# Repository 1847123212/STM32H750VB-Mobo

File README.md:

# STM32H750VB-Mobo
Motherboard for STM32H750VB Coreboard

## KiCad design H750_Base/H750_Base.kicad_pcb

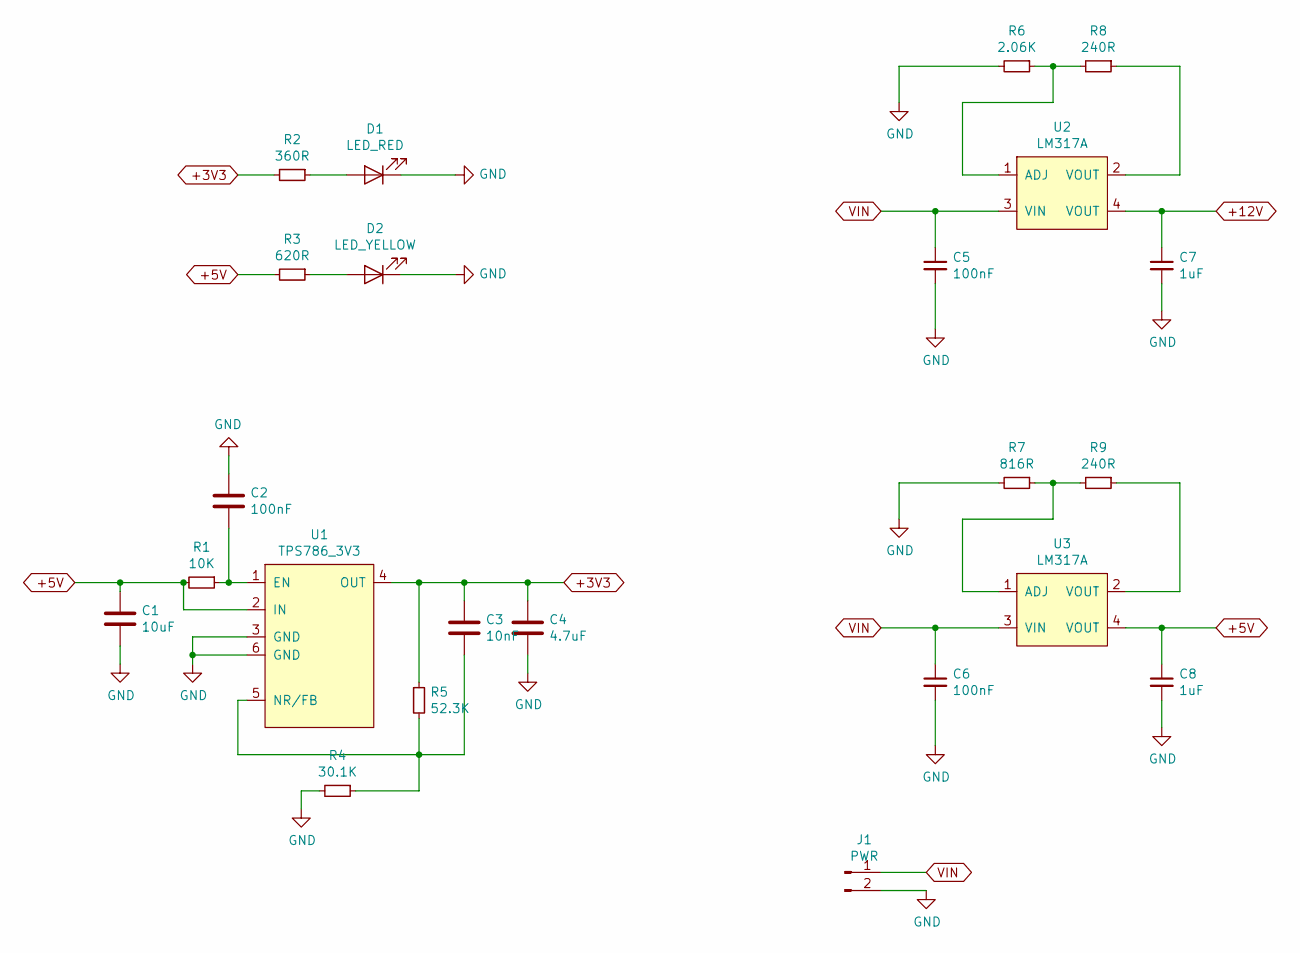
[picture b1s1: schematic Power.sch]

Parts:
C1: 10uF; C_0603_1608Metric
C2: 100nF; C_0603_1608Metric
C3: 10nF; C_0603_1608Metric
C4: 4.7uF; C_0603_1608Metric
C5, C6: 100nF; C_1206_3216Metric
C7, C8: 1uF; C_0805_2012Metric
D1: LED_RED; LED_0603_1608Metric
D2: LED_YELLOW; LED_0603_1608Metric
J1: PWR; PhoenixContact_MSTBVA_2,5_2-G-5,08_1x02_P5.08mm_Vertical
R1: 10K; R_0603_1608Metric
R2: 360R; R_0603_1608Metric
R3: 620R; R_0603_1608Metric
R4: 30.1K; R_0603_1608Metric
R5: 52.3K; R_0603_1608Metric
R6: 2.06K; R_0603_1608Metric
R7: 816R; R_0603_1608Metric
R8, R9: 240R; R_0603_1608Metric
U1: TPS786_3V3; SOT-223-6
U2, U3: LM317A; SOT-223

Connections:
+3V3: C3.1, C4.1, R2.2, R5.1, U1.4 (OUT); also elsewhere on the board
+5V: C1.1, C8.1, R1.2, R3.2, U1.2 (IN), U3.4 (VOUT); also elsewhere on the board
+12V: C7.1, U2.4 (VOUT); also elsewhere on the board
GND: C1.2, C2.1, C4.2, C5.2, C6.2, C7.2, C8.2, D1.1 (K), D2.1 (K), J1.2, R4.2, R6.2, R7.2, U1.3 (GND), U1.6 (GND); also elsewhere on the board
unnamed: C2.2, R1.1, U1.1 (EN)
unnamed: C3.2, R4.1, R5.2, U1.5 (NR/FB)
unnamed 87: D1.2 (A), R2.1; also elsewhere on the board
unnamed 88: D2.2 (A), R3.1; also elsewhere on the board
unnamed: R6.1, R8.2, U2.1 (ADJ)
unnamed: R7.1, R9.2, U3.1 (ADJ)
unnamed: R8.1, U2.2 (VOUT)
unnamed: R9.1, U3.2 (VOUT)
VIN: C5.1, C6.1, J1.1, U2.3 (VIN), U3.3 (VIN); also elsewhere on the board

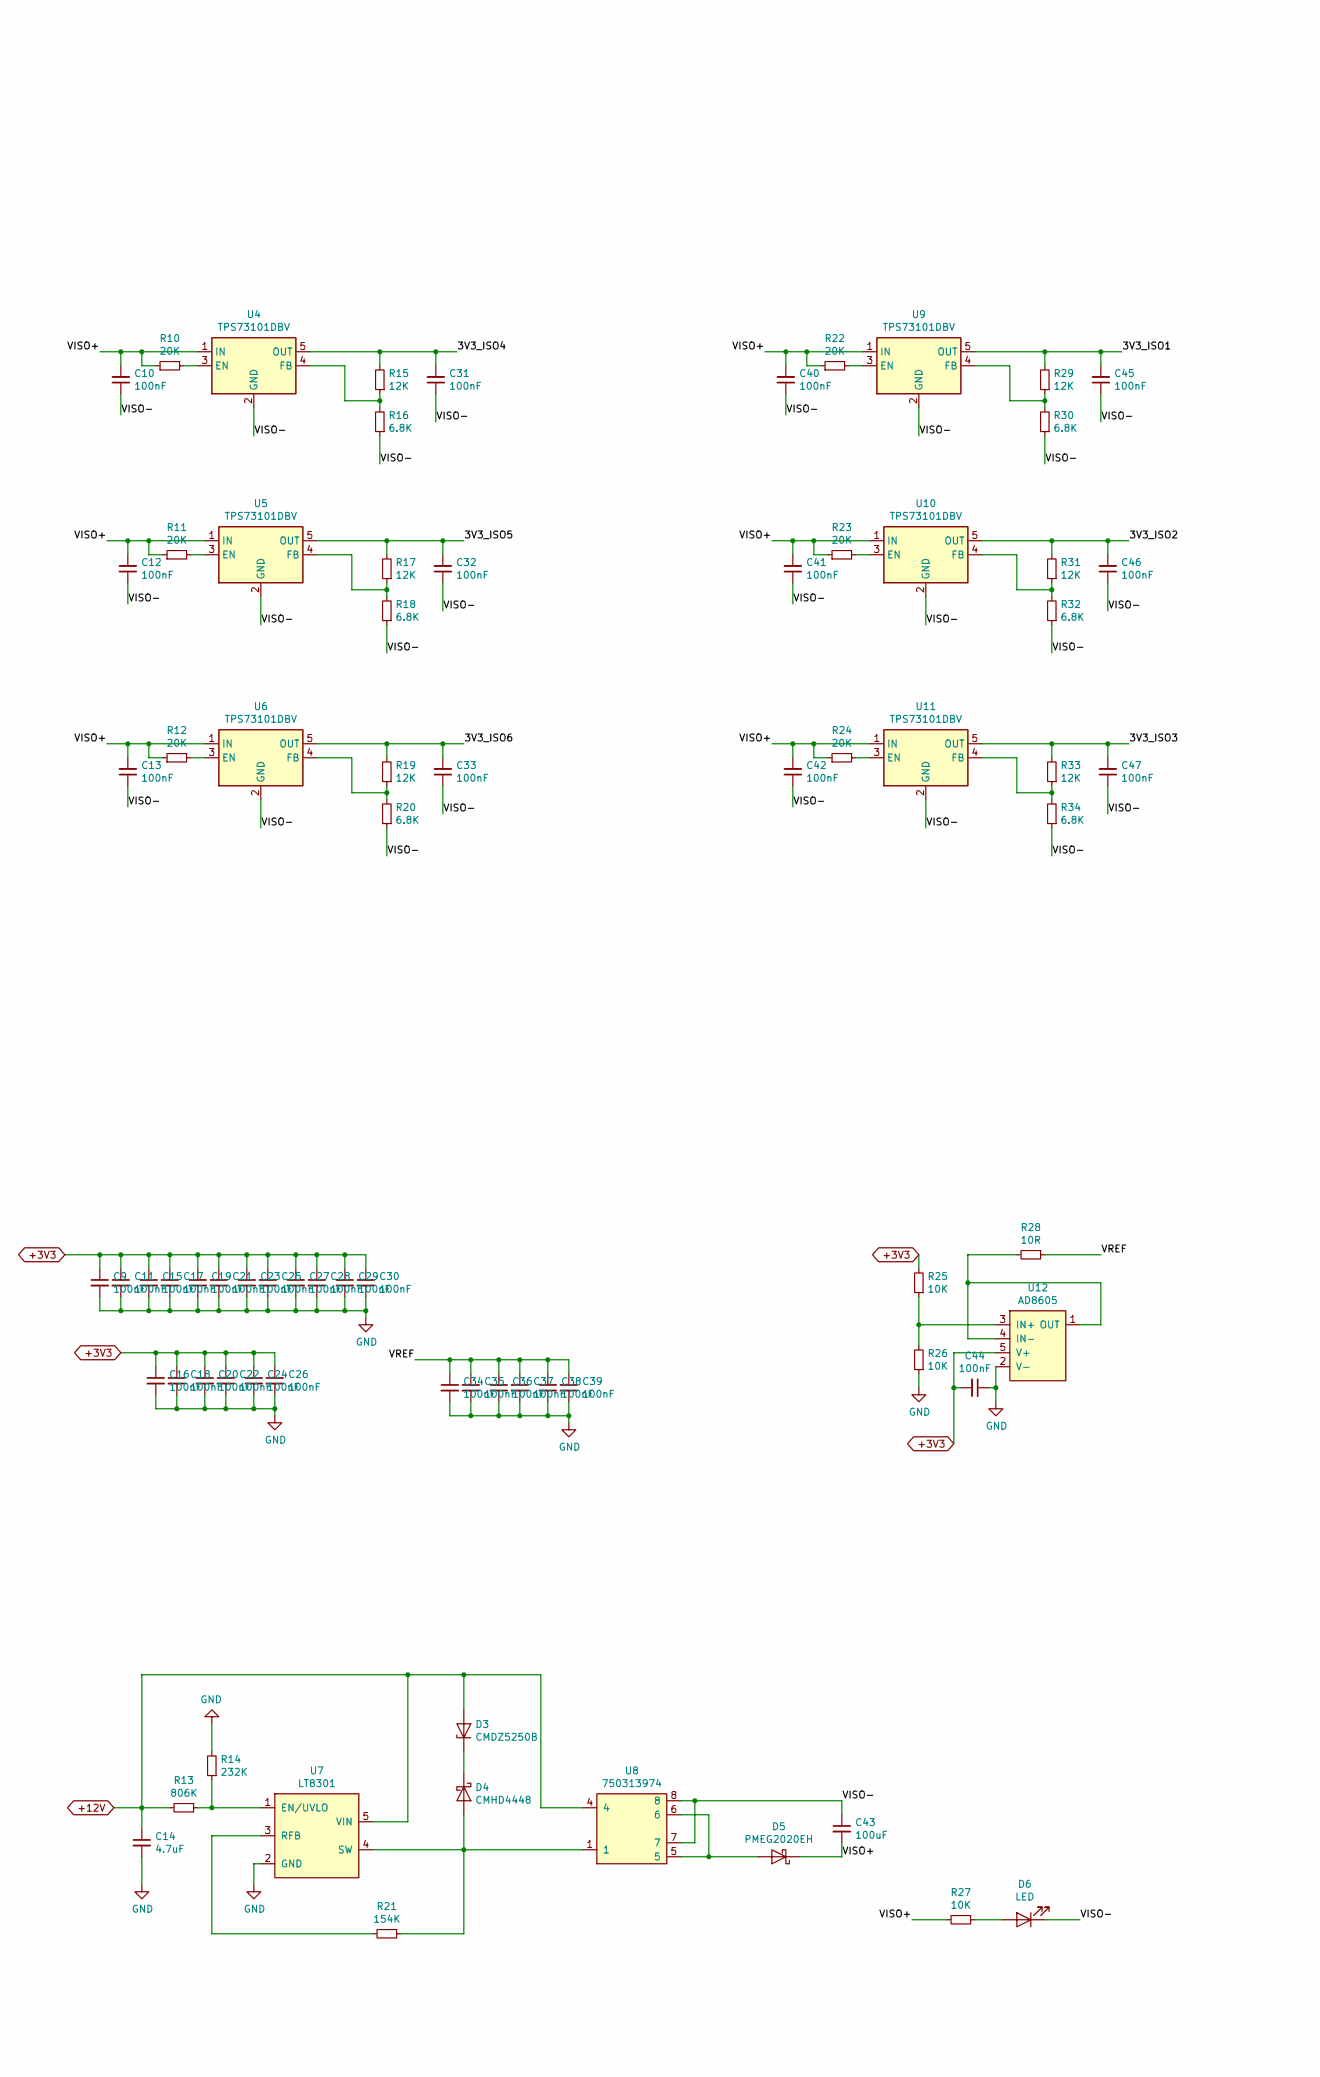
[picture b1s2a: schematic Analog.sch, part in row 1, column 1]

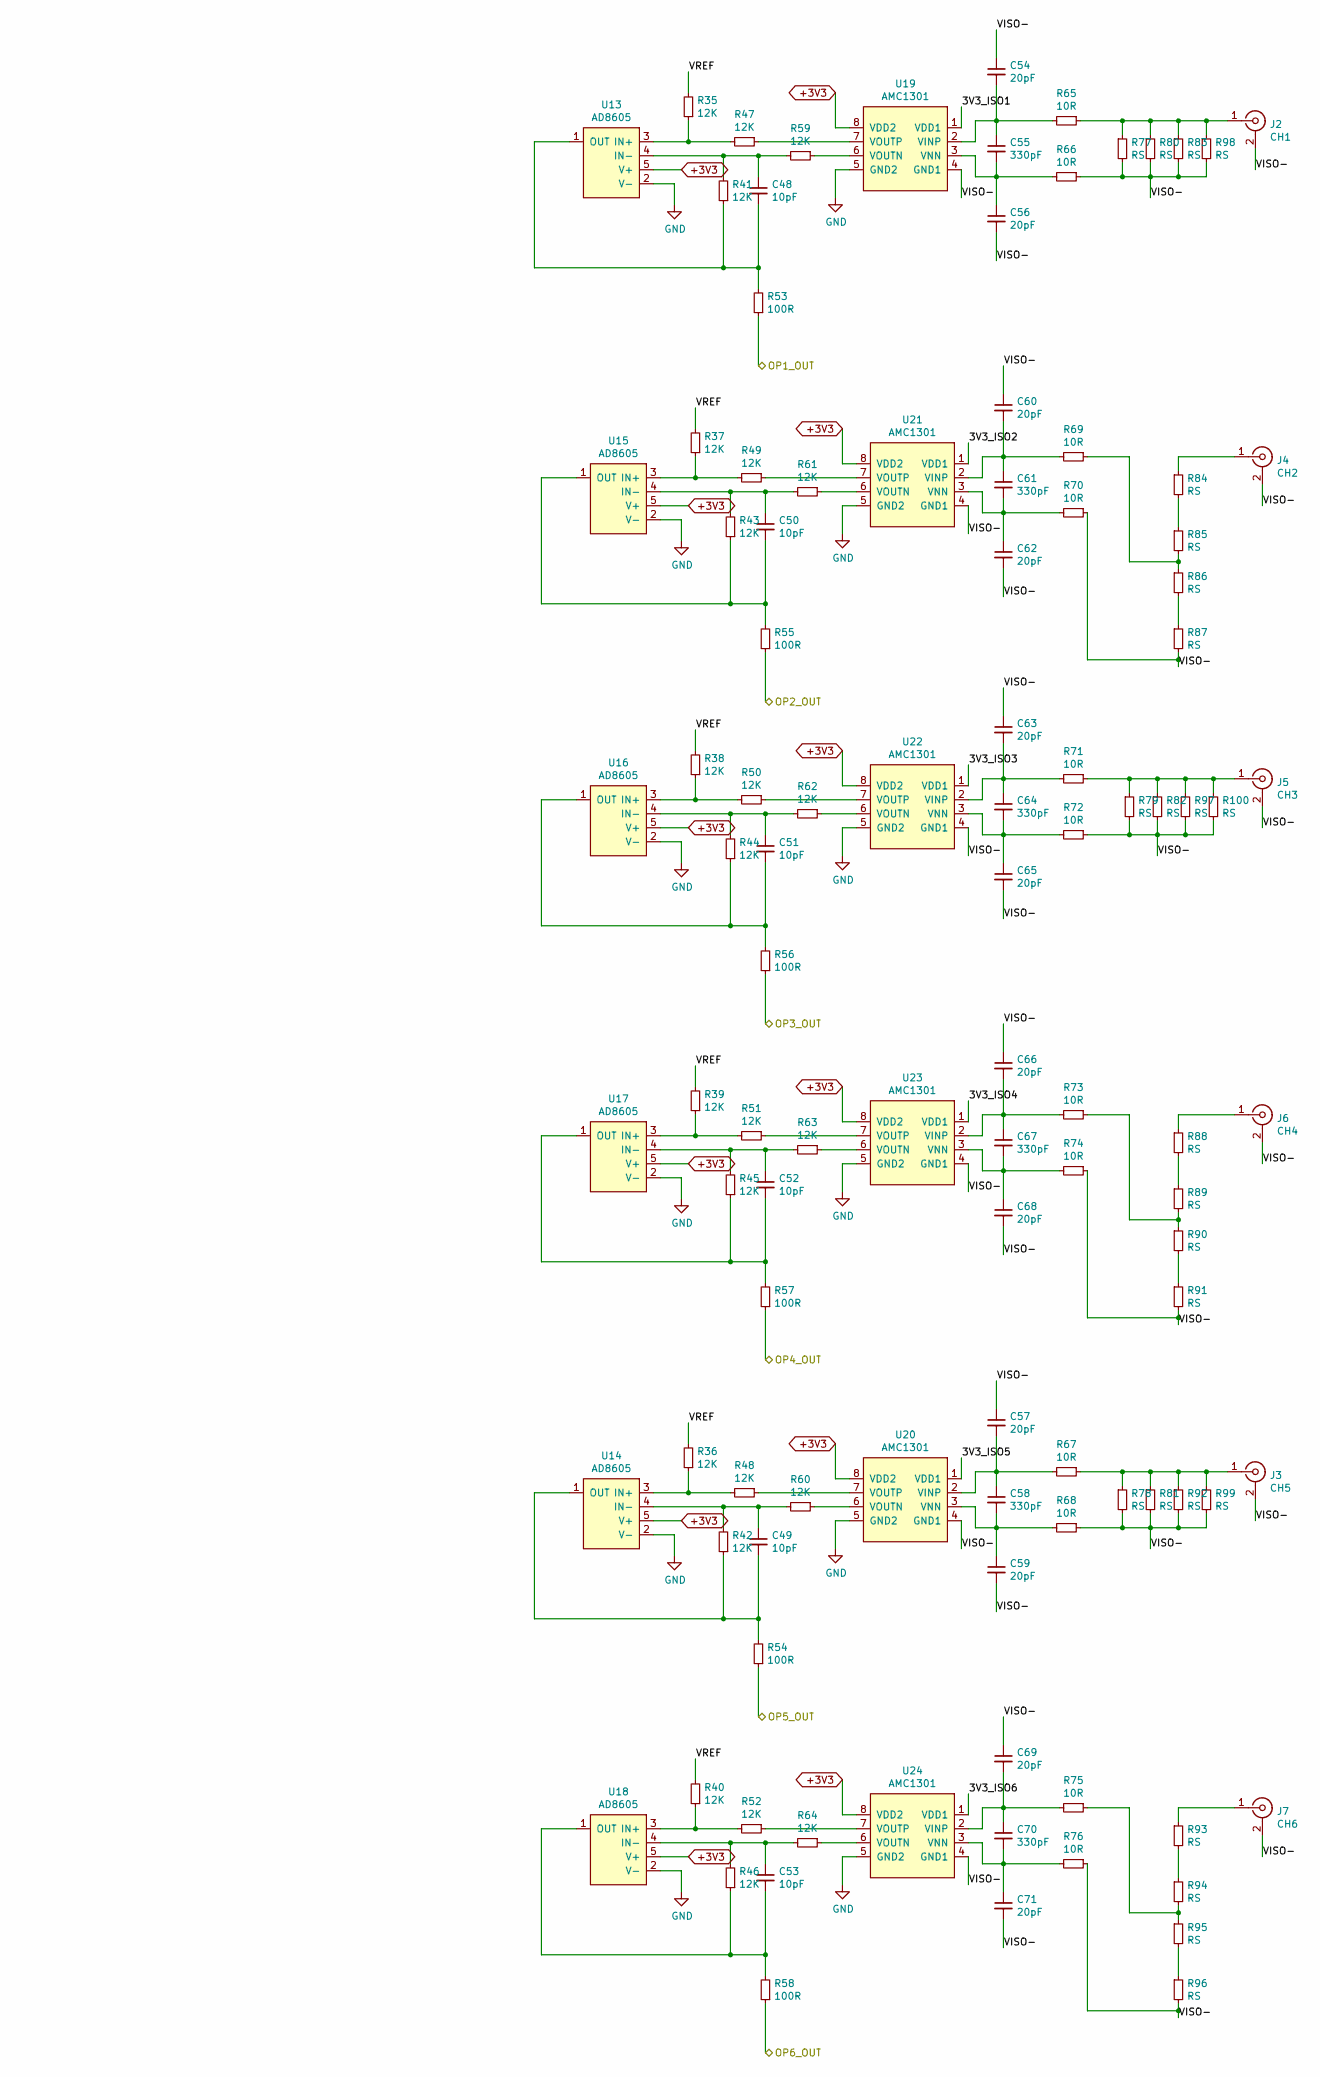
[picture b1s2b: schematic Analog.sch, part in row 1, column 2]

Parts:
C9, C10, C11, C12, C13, C15, C16, C17, C18, C19, C20, C21, C22, C23, C24, C25, C26, C27, C28, C29, C30, C31, C32, C33, C34, C35, C36, C37, C38, C39, C40, C41, C42, C44, C45, C46, C47: 100nF; C_0603_1608Metric
C14: 4.7uF; C_0805_2012Metric
C43: 100uF; C_0603_1608Metric
C48, C49, C50, C51, C52, C53: 10pF; C_0603_1608Metric
C54, C56, C57, C59, C60, C62, C63, C65, C66, C68, C69, C71: 20pF; C_0603_1608Metric
C55, C58, C61, C64, C67, C70: 330pF; C_0603_1608Metric
D3: CMDZ5250B; D_SOD-323
D4: CMHD4448; D_SOD-123
D5: PMEG2020EH; D_SOD-123F
D6: LED; LED_0603_1608Metric
J2: CH1; PhoenixContact_MSTBVA_2,5_2-G-5,08_1x02_P5.08mm_Vertical
J3: CH5; PhoenixContact_MSTBVA_2,5_2-G-5,08_1x02_P5.08mm_Vertical
J4: CH2; PhoenixContact_MSTBVA_2,5_2-G-5,08_1x02_P5.08mm_Vertical
J5: CH3; PhoenixContact_MSTBVA_2,5_2-G-5,08_1x02_P5.08mm_Vertical
J6: CH4; PhoenixContact_MSTBVA_2,5_2-G-5,08_1x02_P5.08mm_Vertical
J7: CH6; PhoenixContact_MSTBVA_2,5_2-G-5,08_1x02_P5.08mm_Vertical
R10, R11, R12, R22, R23, R24: 20K; R_0603_1608Metric
R13: 806K; R_0603_1608Metric
R14: 232K; R_0603_1608Metric
R15, R17, R19, R29, R31, R33, R35, R36, R37, R38, R39, R40, R41, R42, R43, R44, R45, R46, R47, R48, R49, R50, R51, R52, R59, R60, R61, R62, R63, R64: 12K; R_0603_1608Metric
R16, R18, R20, R30, R32, R34: 6.8K; R_0603_1608Metric
R21: 154K; R_0603_1608Metric
R25, R26, R27: 10K; R_0603_1608Metric
R28, R65, R66, R67, R68, R69, R70, R71, R72, R73, R74, R75, R76: 10R; R_0603_1608Metric
R53, R54, R55, R56, R57, R58: 100R; R_0603_1608Metric
R77, R78, R79, R80, R81, R82, R83, R84, R85, R86, R87, R88, R89, R90, R91, R92, R93, R94, R95, R96, R97, R98, R99, R100: RS; R_1206_3216Metric
U4, U5, U6, U9, U10, U11: TPS73101DBV; SOT-23-5
U7: LT8301; SOT-23-5
U8: 750313974
U12, U13, U14, U15, U16, U17, U18: AD8605; SOT-23-5
U19, U20, U21, U22, U23, U24: AMC1301; SOIC-8_7.5x5.85mm_P1.27mm

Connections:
+3V3: C9.1, C11.1, C15.1, C16.1, C17.1, C18.1, C19.1, C20.1, C21.1, C22.1, C23.1, C24.1, C25.1, C26.1, C27.1, C28.1, C29.1, C30.1, C44.2, R25.2, U12.5 (V+), U13.5 (V+), U14.5 (V+), U15.5 (V+), U16.5 (V+), U17.5 (V+), U18.5 (V+), U19.8 (VDD2), U20.8 (VDD2), U21.8 (VDD2), U22.8 (VDD2), U23.8 (VDD2), U24.8 (VDD2); also elsewhere on the board
+12V: C14.1, D3.2 (A), R13.2, U7.5 (VIN), U8.4; also elsewhere on the board
/U_ADC/AD_CH1: R53.1; also elsewhere on the board
/U_ADC/AD_CH2: R55.1; also elsewhere on the board
/U_ADC/AD_CH3: R56.1; also elsewhere on the board
/U_ADC/AD_CH4: R57.1; also elsewhere on the board
/U_ADC/AD_CH5: R54.1; also elsewhere on the board
/U_ADC/AD_CH6: R58.1; also elsewhere on the board
/U_Analog/3V3_ISO1: C45.2, R29.2, U9.5 (OUT), U19.1 (VDD1)
/U_Analog/3V3_ISO2: C46.2, R31.2, U10.5 (OUT), U21.1 (VDD1)
/U_Analog/3V3_ISO3: C47.2, R33.2, U11.5 (OUT), U22.1 (VDD1)
/U_Analog/3V3_ISO4: C31.2, R15.2, U4.5 (OUT), U23.1 (VDD1)
/U_Analog/3V3_ISO5: C32.2, R17.2, U5.5 (OUT), U20.1 (VDD1)
/U_Analog/3V3_ISO6: C33.2, R19.2, U6.5 (OUT), U24.1 (VDD1)
/U_Analog/VISO+: C10.2, C12.2, C13.2, C40.2, C41.2, C42.2, C43.2, D5.1 (K), R10.1, R11.1, R12.1, R22.1, R23.1, R24.1, R27.2, U4.1 (IN), U5.1 (IN), U6.1 (IN), U9.1 (IN), U10.1 (IN), U11.1 (IN)
/U_Analog/VISO-: C10.1, C12.1, C13.1, C31.1, C32.1, C33.1, C40.1, C41.1, C42.1, C43.1, C45.1, C46.1, C47.1, C54.1, C56.2, C57.1, C59.2, C60.1, C62.2, C63.1, C65.2, C66.1, C68.2, C69.1, C71.2, D6.1 (K), J2.2 (Ext), J3.2 (Ext), J4.2 (Ext), J5.2 (Ext), J6.2 (Ext), J7.2 (Ext), R16.1, R18.1, R20.1, R30.1, R32.1, R34.1, R66.1, R68.1, R70.1, R72.1, R74.1, R76.1, R77.2, R78.2, R79.2, R80.2, R81.2, R82.2, R83.2, R87.2, R91.2, R92.2, R96.2, R97.2, R98.2, R99.2, R100.2, U4.2 (GND), U5.2 (GND), U6.2 (GND), U8.7, U8.8, U9.2 (GND), U10.2 (GND), U11.2 (GND), U19.4 (GND1), U20.4 (GND1), U21.4 (GND1), U22.4 (GND1), U23.4 (GND1), U24.4 (GND1); also elsewhere on the board
/U_Analog/VREF: C34.1, C35.1, C36.1, C37.1, C38.1, C39.1, R28.1, R35.2, R36.2, R37.2, R38.2, R39.2, R40.2
GND: C9.2, C11.2, C14.2, C15.2, C16.2, C17.2, C18.2, C19.2, C20.2, C21.2, C22.2, C23.2, C24.2, C25.2, C26.2, C27.2, C28.2, C29.2, C30.2, C34.2, C35.2, C36.2, C37.2, C38.2, C39.2, C44.1, R14.2, R26.1, U7.2 (GND), U12.2 (V-), U13.2 (V-), U14.2 (V-), U15.2 (V-), U16.2 (V-), U17.2 (V-), U18.2 (V-), U19.5 (GND2), U20.5 (GND2), U21.5 (GND2), U22.5 (GND2), U23.5 (GND2), U24.5 (GND2); also elsewhere on the board
unnamed: C48.1, R41.2, R59.2, U13.4 (IN-)
unnamed: C48.2, R41.1, R53.2, U13.1 (OUT)
unnamed: C49.1, R42.2, R60.2, U14.4 (IN-)
unnamed: C49.2, R42.1, R54.2, U14.1 (OUT)
unnamed: C50.1, R43.2, R61.2, U15.4 (IN-)
unnamed: C50.2, R43.1, R55.2, U15.1 (OUT)
unnamed: C51.1, R44.2, R62.2, U16.4 (IN-)
unnamed: C51.2, R44.1, R56.2, U16.1 (OUT)
unnamed: C52.1, R45.2, R63.2, U17.4 (IN-)
unnamed: C52.2, R45.1, R57.2, U17.1 (OUT)
unnamed: C53.1, R46.2, R64.2, U18.4 (IN-)
unnamed: C53.2, R46.1, R58.2, U18.1 (OUT)
unnamed: C54.2, C55.1, R65.2, U19.2 (VINP)
unnamed: C55.2, C56.1, R66.2, U19.3 (VNN)
unnamed: C57.2, C58.1, R67.2, U20.2 (VINP)
unnamed: C58.2, C59.1, R68.2, U20.3 (VNN)
unnamed: C60.2, C61.1, R69.2, U21.2 (VINP)
unnamed: C61.2, C62.1, R70.2, U21.3 (VNN)
unnamed: C63.2, C64.1, R71.2, U22.2 (VINP)
unnamed: C64.2, C65.1, R72.2, U22.3 (VNN)
unnamed: C66.2, C67.1, R73.2, U23.2 (VINP)
unnamed: C67.2, C68.1, R74.2, U23.3 (VNN)
unnamed: C69.2, C70.1, R75.2, U24.2 (VINP)
unnamed: C70.2, C71.1, R76.2, U24.3 (VNN)
unnamed: D3.1 (K), D4.1 (K)
unnamed: D4.2 (A), R21.1, U7.4 (SW), U8.1
unnamed: D5.2 (A), U8.5, U8.6
unnamed 92: D6.2 (A), R27.1; also elsewhere on the board
unnamed 97: J2.1 (In), R65.1, R77.1, R80.1, R83.1, R98.1; also elsewhere on the board
unnamed 98: J3.1 (In), R67.1, R78.1, R81.1, R92.1, R99.1; also elsewhere on the board
unnamed 99: J4.1 (In), R84.1; also elsewhere on the board
unnamed 100: J5.1 (In), R71.1, R79.1, R82.1, R97.1, R100.1; also elsewhere on the board
unnamed 101: J6.1 (In), R88.1; also elsewhere on the board
unnamed 102: J7.1 (In), R93.1; also elsewhere on the board
unnamed: R10.2, U4.3 (EN)
unnamed: R11.2, U5.3 (EN)
unnamed: R12.2, U6.3 (EN)
unnamed: R13.1, R14.1, U7.1 (EN/UVLO)
unnamed: R15.1, R16.2, U4.4 (FB)
unnamed: R17.1, R18.2, U5.4 (FB)
unnamed: R19.1, R20.2, U6.4 (FB)
unnamed: R21.2, U7.3 (RFB)
unnamed: R22.2, U9.3 (EN)
unnamed: R23.2, U10.3 (EN)
unnamed: R24.2, U11.3 (EN)
unnamed: R25.1, R26.2, U12.3 (IN+)
unnamed: R28.2, U12.1 (OUT), U12.4 (IN-)
unnamed: R29.1, R30.2, U9.4 (FB)
unnamed: R31.1, R32.2, U10.4 (FB)
unnamed: R33.1, R34.2, U11.4 (FB)
unnamed: R35.1, R47.2, U13.3 (IN+)
unnamed: R36.1, R48.2, U14.3 (IN+)
unnamed: R37.1, R49.2, U15.3 (IN+)
unnamed: R38.1, R50.2, U16.3 (IN+)
unnamed: R39.1, R51.2, U17.3 (IN+)
unnamed: R40.1, R52.2, U18.3 (IN+)
unnamed: R47.1, U19.7 (VOUTP)
unnamed: R48.1, U20.7 (VOUTP)
unnamed: R49.1, U21.7 (VOUTP)
unnamed: R50.1, U22.7 (VOUTP)
unnamed: R51.1, U23.7 (VOUTP)
unnamed: R52.1, U24.7 (VOUTP)
unnamed: R59.1, U19.6 (VOUTN)
unnamed: R60.1, U20.6 (VOUTN)
unnamed: R61.1, U21.6 (VOUTN)
unnamed: R62.1, U22.6 (VOUTN)
unnamed: R63.1, U23.6 (VOUTN)
unnamed: R64.1, U24.6 (VOUTN)
unnamed: R69.1, R85.2, R86.1
unnamed: R73.1, R89.2, R90.1
unnamed: R75.1, R94.2, R95.1
unnamed: R84.2, R85.1
unnamed: R86.2, R87.1
unnamed: R88.2, R89.1
unnamed: R90.2, R91.1
unnamed: R93.2, R94.1
unnamed: R95.2, R96.1

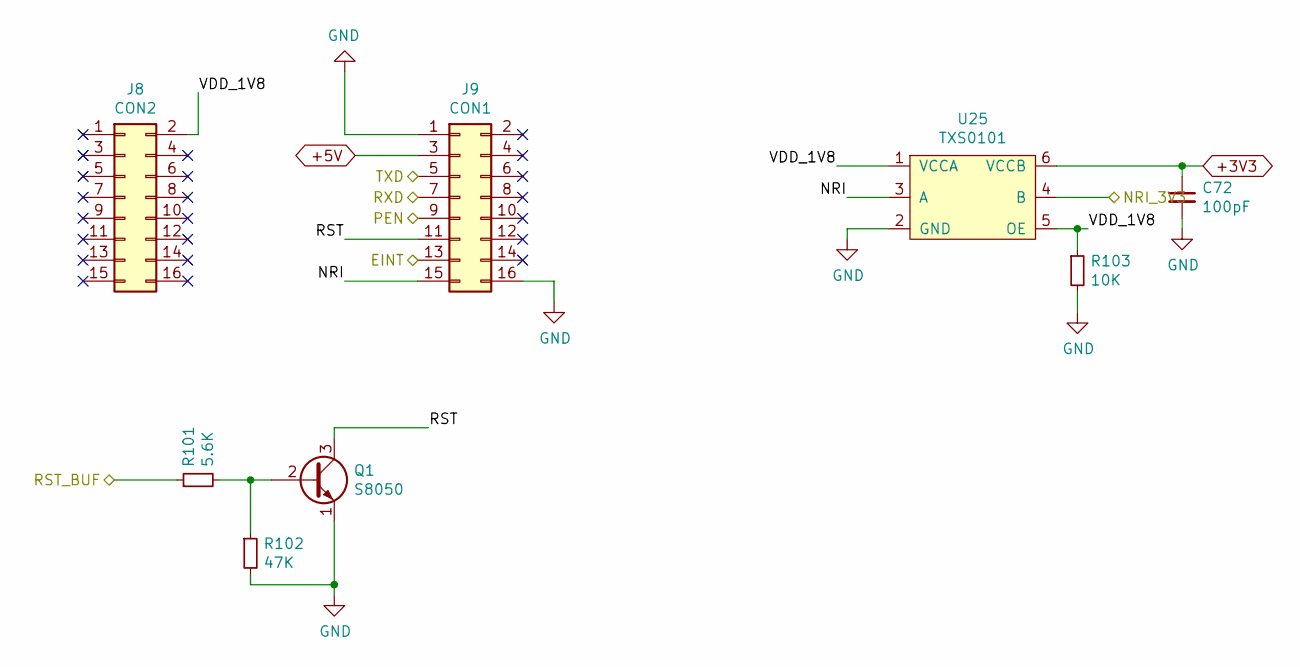
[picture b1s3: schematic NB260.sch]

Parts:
C72: 100pF; C_0603_1608Metric
J8: CON2; PinHeader_2x08_P2.54mm_Vertical
J9: CON1; PinHeader_2x08_P2.54mm_Vertical
Q1: S8050; SOT-23
R101: 5.6K; R_0603_1608Metric
R102: 47K; R_0603_1608Metric
R103: 10K; R_0603_1608Metric
U25: TXS0101; SOT-23-6

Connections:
+3V3: C72.1, U25.6 (VCCB); also elsewhere on the board
+5V: J9.3; also elsewhere on the board
/U_Connectors/EINT: J9.13; also elsewhere on the board
/U_Connectors/NRI: U25.4 (B); also elsewhere on the board
/U_Connectors/PEN: J9.9; also elsewhere on the board
/U_Connectors/RST: R101.1; also elsewhere on the board
/U_Connectors/RXD: J9.7; also elsewhere on the board
/U_Connectors/TXD: J9.5; also elsewhere on the board
/U_NB260/NRI: J9.15, U25.3 (A)
/U_NB260/RST: J9.11, Q1.3 (C)
/U_NB260/VDD_1V8: J8.2, R103.1, U25.1 (VCCA), U25.5 (OE)
GND: C72.2, J9.1, J9.16, Q1.1 (E), R102.2, R103.2, U25.2 (GND); also elsewhere on the board
unnamed: Q1.2 (B), R101.2, R102.1

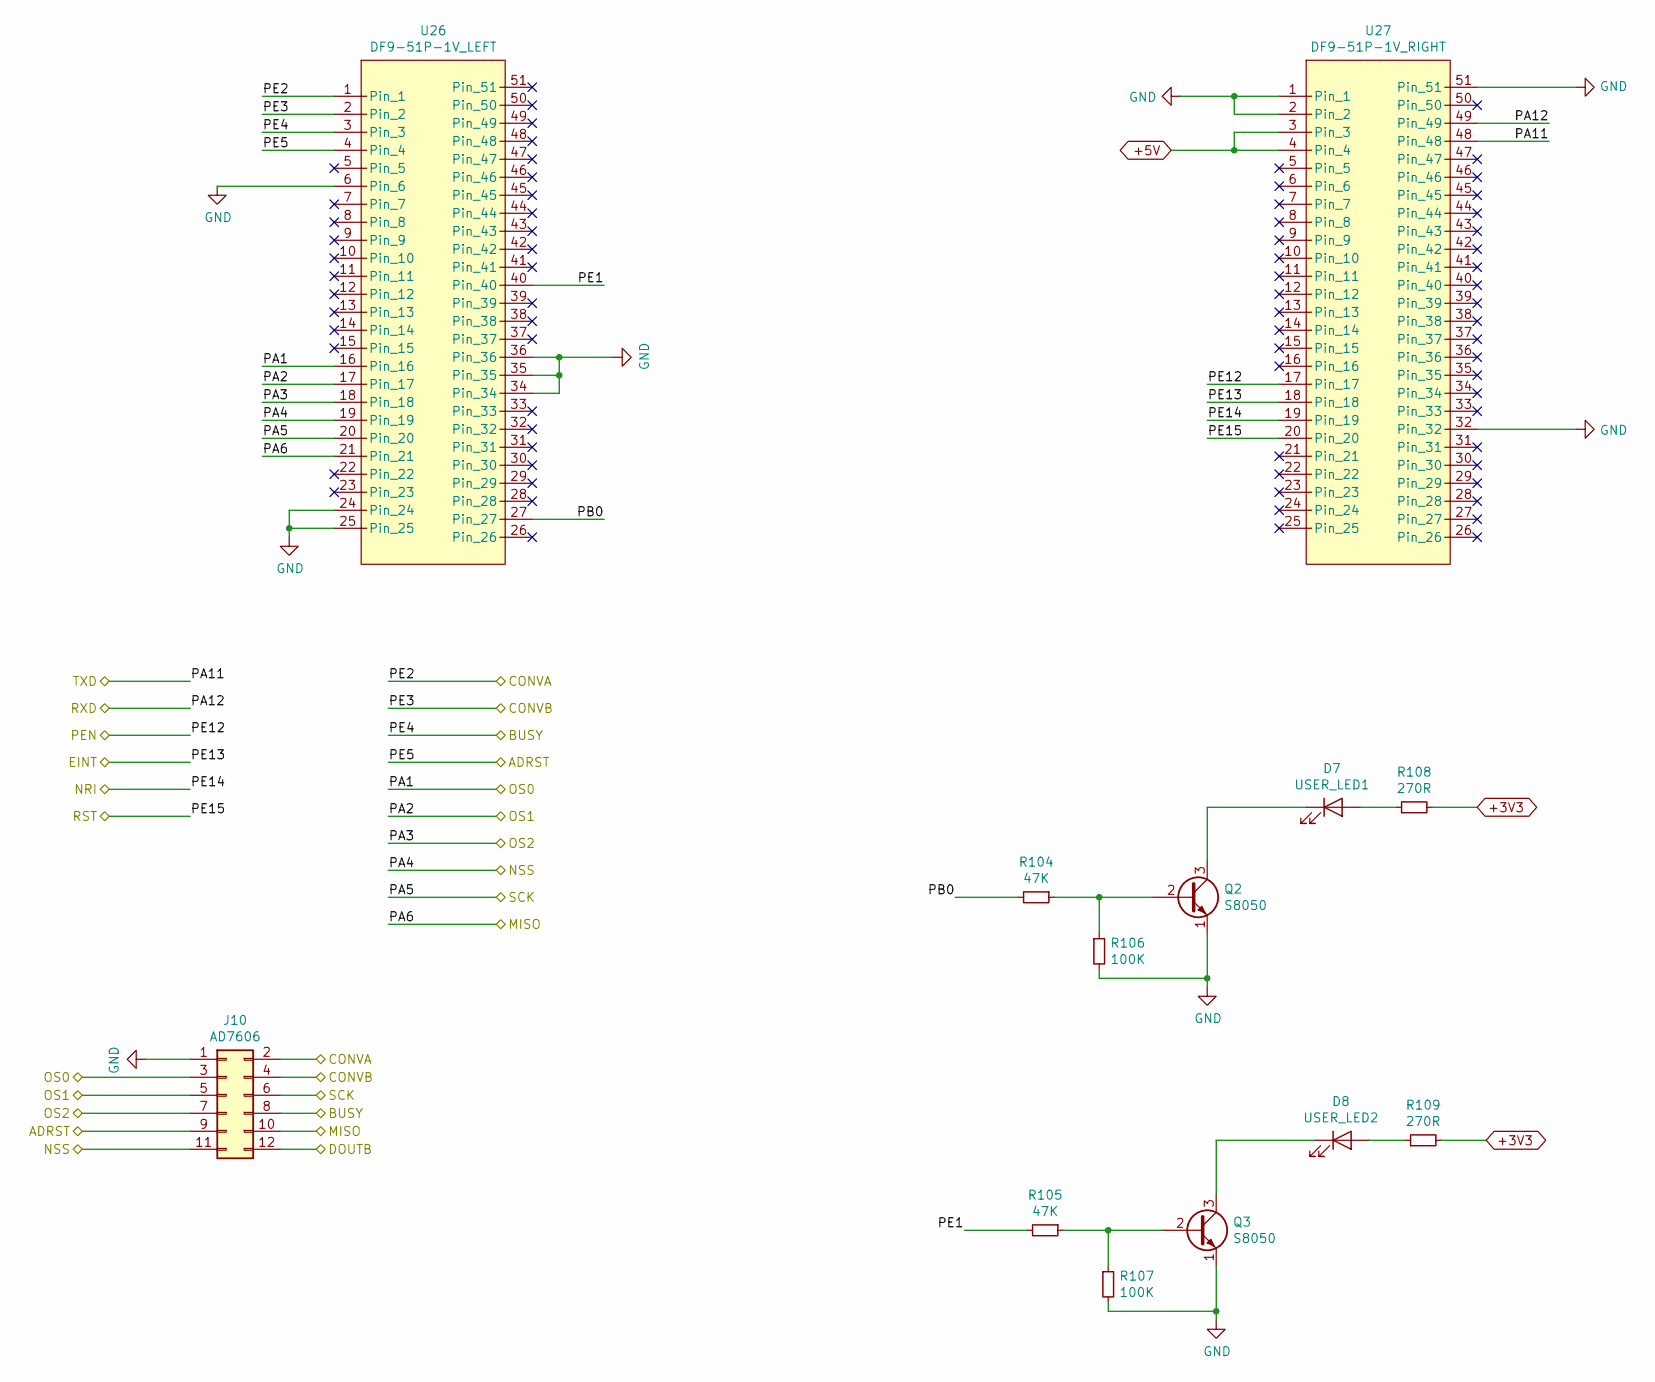
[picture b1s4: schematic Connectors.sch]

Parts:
D7: USER_LED1; LED_0603_1608Metric
D8: USER_LED2; LED_0603_1608Metric
J10: AD7606; PinHeader_2x06_P2.54mm_Vertical
Q2, Q3: S8050; SOT-23
R104, R105: 47K; R_0603_1608Metric
R106, R107: 100K; R_0603_1608Metric
R108, R109: 270R; R_0603_1608Metric
U26: DF9-51P-1V_LEFT; DF9-2
U27: DF9-51P-1V_RIGHT; DF9-2

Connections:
+3V3: R108.2, R109.2; also elsewhere on the board
+5V: U27.3, U27.4; also elsewhere on the board
/U_ADC/BUSY: J10.8, U26.3; also elsewhere on the board
/U_ADC/CONVA: J10.2, U26.1; also elsewhere on the board
/U_ADC/CONVB: J10.4, U26.2; also elsewhere on the board
/U_ADC/CS: J10.11, U26.19; also elsewhere on the board
/U_ADC/DOUTA: J10.10, U26.21; also elsewhere on the board
/U_ADC/OS0: J10.3, U26.16; also elsewhere on the board
/U_ADC/OS1: J10.5, U26.17; also elsewhere on the board
/U_ADC/OS2: J10.7, U26.18; also elsewhere on the board
/U_Connectors/ADRST: J10.9, U26.4; also elsewhere on the board
/U_Connectors/EINT: U27.18; also elsewhere on the board
/U_Connectors/NRI: U27.19; also elsewhere on the board
/U_Connectors/PB0: R104.2, U26.27
/U_Connectors/PE1: R105.2, U26.40
/U_Connectors/PEN: U27.17; also elsewhere on the board
/U_Connectors/RST: U27.20; also elsewhere on the board
/U_Connectors/RXD: U27.49; also elsewhere on the board
/U_Connectors/SCK: J10.6, U26.20; also elsewhere on the board
/U_Connectors/TXD: U27.48; also elsewhere on the board
GND: J10.1, Q2.1 (E), Q3.1 (E), R106.2, R107.2, U26.6, U26.24, U26.25, U26.34, U26.35, U26.36, U27.1, U27.2, U27.32, U27.51; also elsewhere on the board
unnamed 93: D7.1 (K), Q2.3 (C); also elsewhere on the board
unnamed 94: D7.2 (A), R108.1; also elsewhere on the board
unnamed 95: D8.1 (K), Q3.3 (C); also elsewhere on the board
unnamed 96: D8.2 (A), R109.1; also elsewhere on the board
unnamed: Q2.2 (B), R104.1, R106.1
unnamed: Q3.2 (B), R105.1, R107.1

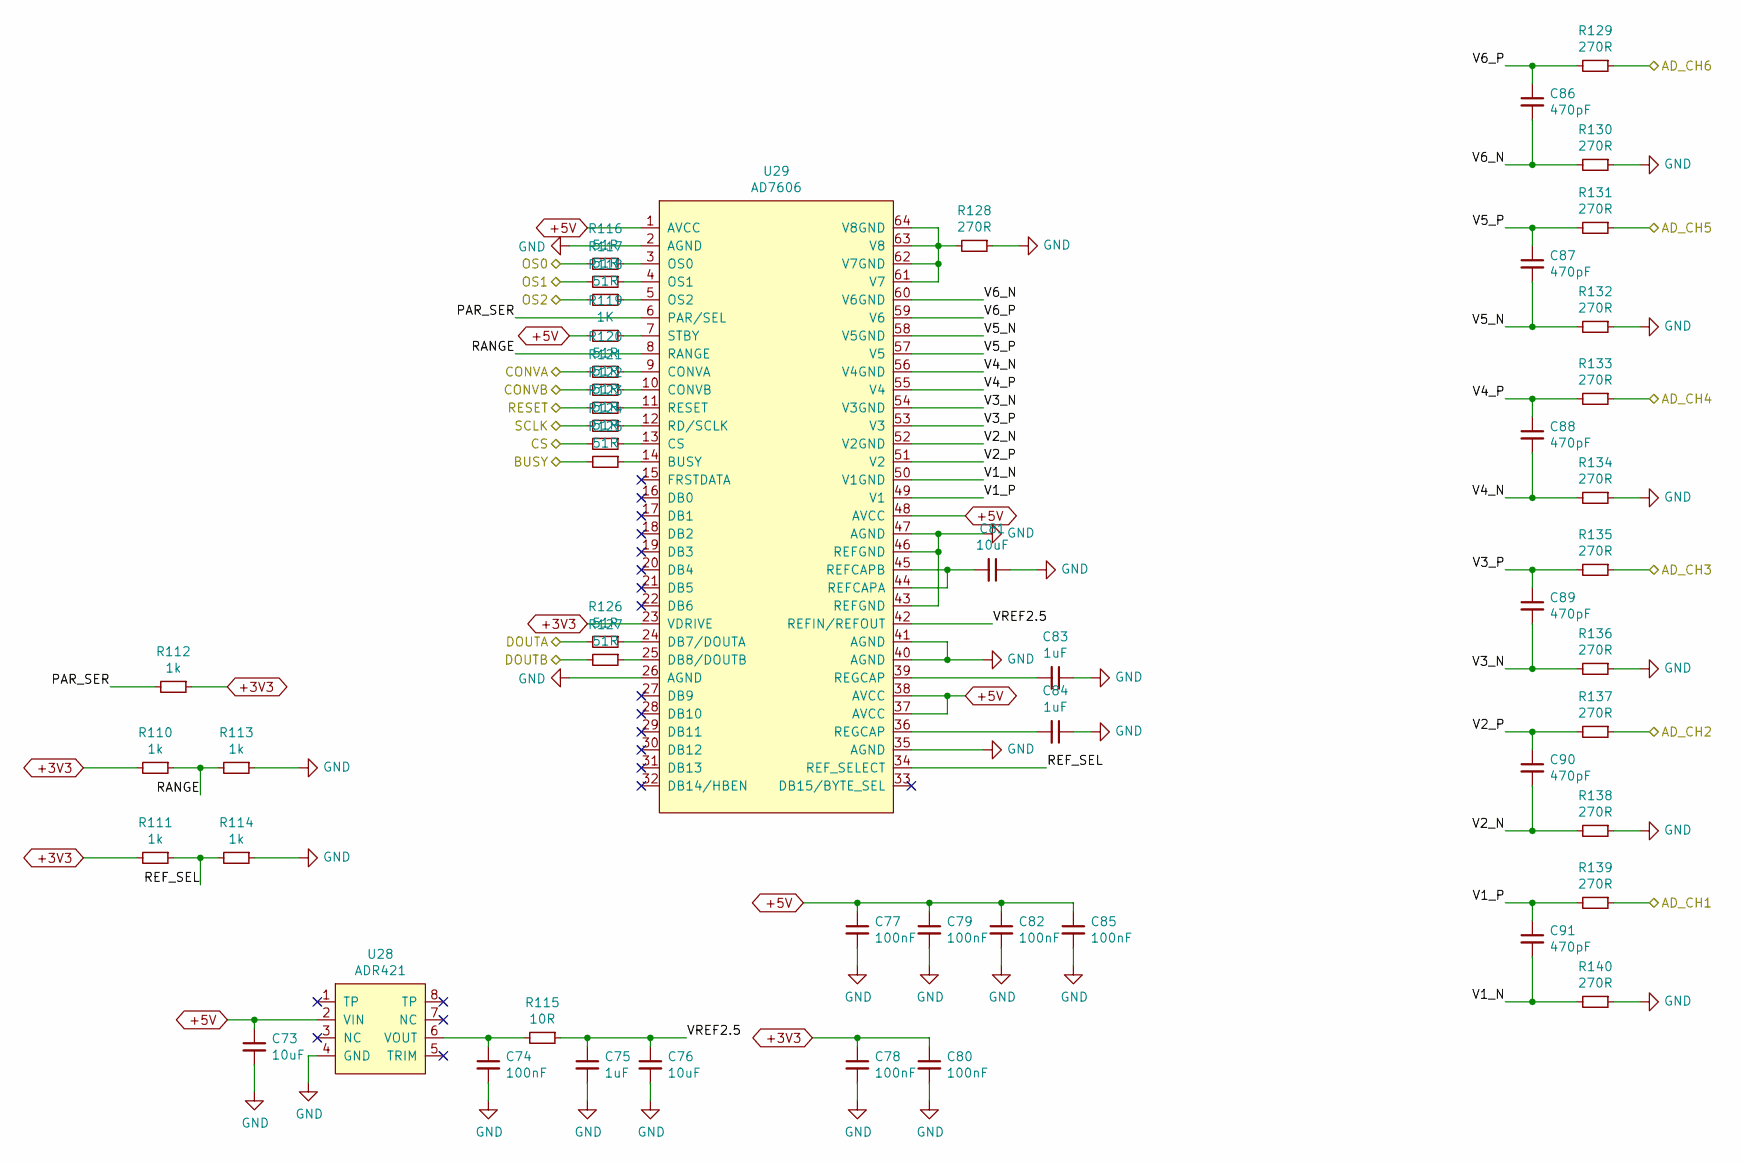
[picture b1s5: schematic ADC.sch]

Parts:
C73, C76, C81: 10uF; C_0603_1608Metric
C74, C77, C78, C79, C80, C82, C85: 100nF; C_0603_1608Metric
C75, C83, C84: 1uF; C_0603_1608Metric
C86, C87, C88, C89, C90, C91: 470pF; C_0603_1608Metric
R110, R111, R112, R113, R114: 1k; R_0603_1608Metric
R115: 10R; R_0603_1608Metric
R116, R117, R118, R120, R121, R122, R123, R124, R125, R126, R127: 51R; R_0603_1608Metric
R119: 1K; R_0603_1608Metric
R128, R129, R130, R131, R132, R133, R134, R135, R136, R137, R138, R139, R140: 270R; R_0603_1608Metric
U28: ADR421; SOIC-8_3.9x4.9mm_P1.27mm
U29: AD7606; LQFP-64_10x10mm_P0.5mm

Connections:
+3V3: C78.1, C80.1, R110.2, R111.2, R112.1, U29.23 (VDRIVE); also elsewhere on the board
+5V: C73.1, C77.1, C79.1, C82.1, C85.1, R119.2, U28.2 (VIN), U29.1 (AVCC), U29.37 (AVCC), U29.38 (AVCC), U29.48 (AVCC); also elsewhere on the board
/U_ADC/AD_CH1: R139.1; also elsewhere on the board
/U_ADC/AD_CH2: R137.1; also elsewhere on the board
/U_ADC/AD_CH3: R135.1; also elsewhere on the board
/U_ADC/AD_CH4: R133.1; also elsewhere on the board
/U_ADC/AD_CH5: R131.1; also elsewhere on the board
/U_ADC/AD_CH6: R129.1; also elsewhere on the board
/U_ADC/BUSY: R125.2; also elsewhere on the board
/U_ADC/CONVA: R120.2; also elsewhere on the board
/U_ADC/CONVB: R121.2; also elsewhere on the board
/U_ADC/CS: R124.2; also elsewhere on the board
/U_ADC/DOUTA: R126.2; also elsewhere on the board
/U_ADC/DOUTB: R127.2; also elsewhere on the board
/U_ADC/OS0: R116.2; also elsewhere on the board
/U_ADC/OS1: R117.2; also elsewhere on the board
/U_ADC/OS2: R118.2; also elsewhere on the board
/U_ADC/PAR_SER: R112.2, U29.6 (PAR/SEL)
/U_ADC/RANGE: R110.1, R113.2, U29.8 (RANGE)
/U_ADC/REF_SEL: R111.1, R114.2, U29.34 (REF_SELECT)
/U_ADC/V1_N: C91.2, R140.2, U29.50 (V1GND)
/U_ADC/V1_P: C91.1, R139.2, U29.49 (V1)
/U_ADC/V2_N: C90.2, R138.2, U29.52 (V2GND)
/U_ADC/V2_P: C90.1, R137.2, U29.51 (V2)
/U_ADC/V3_N: C89.2, R136.2, U29.54 (V3GND)
/U_ADC/V3_P: C89.1, R135.2, U29.53 (V3)
/U_ADC/V4_N: C88.2, R134.2, U29.56 (V4GND)
/U_ADC/V4_P: C88.1, R133.2, U29.55 (V4)
/U_ADC/V5_N: C87.2, R132.2, U29.58 (V5GND)
/U_ADC/V5_P: C87.1, R131.2, U29.57 (V5)
/U_ADC/V6_N: C86.2, R130.2, U29.60 (V6GND)
/U_ADC/V6_P: C86.1, R129.2, U29.59 (V6)
/U_ADC/VREF2.5: C75.1, C76.1, R115.1, U29.42 (REFIN/REFOUT)
/U_Connectors/ADRST: R122.2; also elsewhere on the board
/U_Connectors/SCK: R123.2; also elsewhere on the board
GND: C73.2, C74.2, C75.2, C76.2, C77.2, C78.2, C79.2, C80.2, C81.1, C82.2, C83.1, C84.1, C85.2, R113.1, R114.1, R128.1, R130.1, R132.1, R134.1, R136.1, R138.1, R140.1, U28.4 (GND), U29.2 (AGND), U29.26 (AGND), U29.35 (AGND), U29.40 (AGND), U29.41 (AGND), U29.43 (REFGND), U29.46 (REFGND), U29.47 (AGND); also elsewhere on the board
unnamed: C74.1, R115.2, U28.6 (VOUT)
unnamed: C81.2, U29.44 (REFCAPA), U29.45 (REFCAPB)
unnamed: C83.2, U29.39 (REGCAP)
unnamed: C84.2, U29.36 (REGCAP)
unnamed: R116.1, U29.3 (OS0)
unnamed: R117.1, U29.4 (OS1)
unnamed: R118.1, U29.5 (OS2)
unnamed: R119.1, U29.7 (STBY)
unnamed: R120.1, U29.9 (CONVA)
unnamed: R121.1, U29.10 (CONVB)
unnamed: R122.1, U29.11 (RESET)
unnamed: R123.1, U29.12 (RD/SCLK)
unnamed: R124.1, U29.13 (CS)
unnamed: R125.1, U29.14 (BUSY)
unnamed: R126.1, U29.24 (DB7/DOUTA)
unnamed: R127.1, U29.25 (DB8/DOUTB)
unnamed: R128.2, U29.61 (V7), U29.62 (V7GND), U29.63 (V8), U29.64 (V8GND)
